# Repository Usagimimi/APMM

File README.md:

# APMM
Mother board for Arduino Pro Mini to work with Mysensors.org

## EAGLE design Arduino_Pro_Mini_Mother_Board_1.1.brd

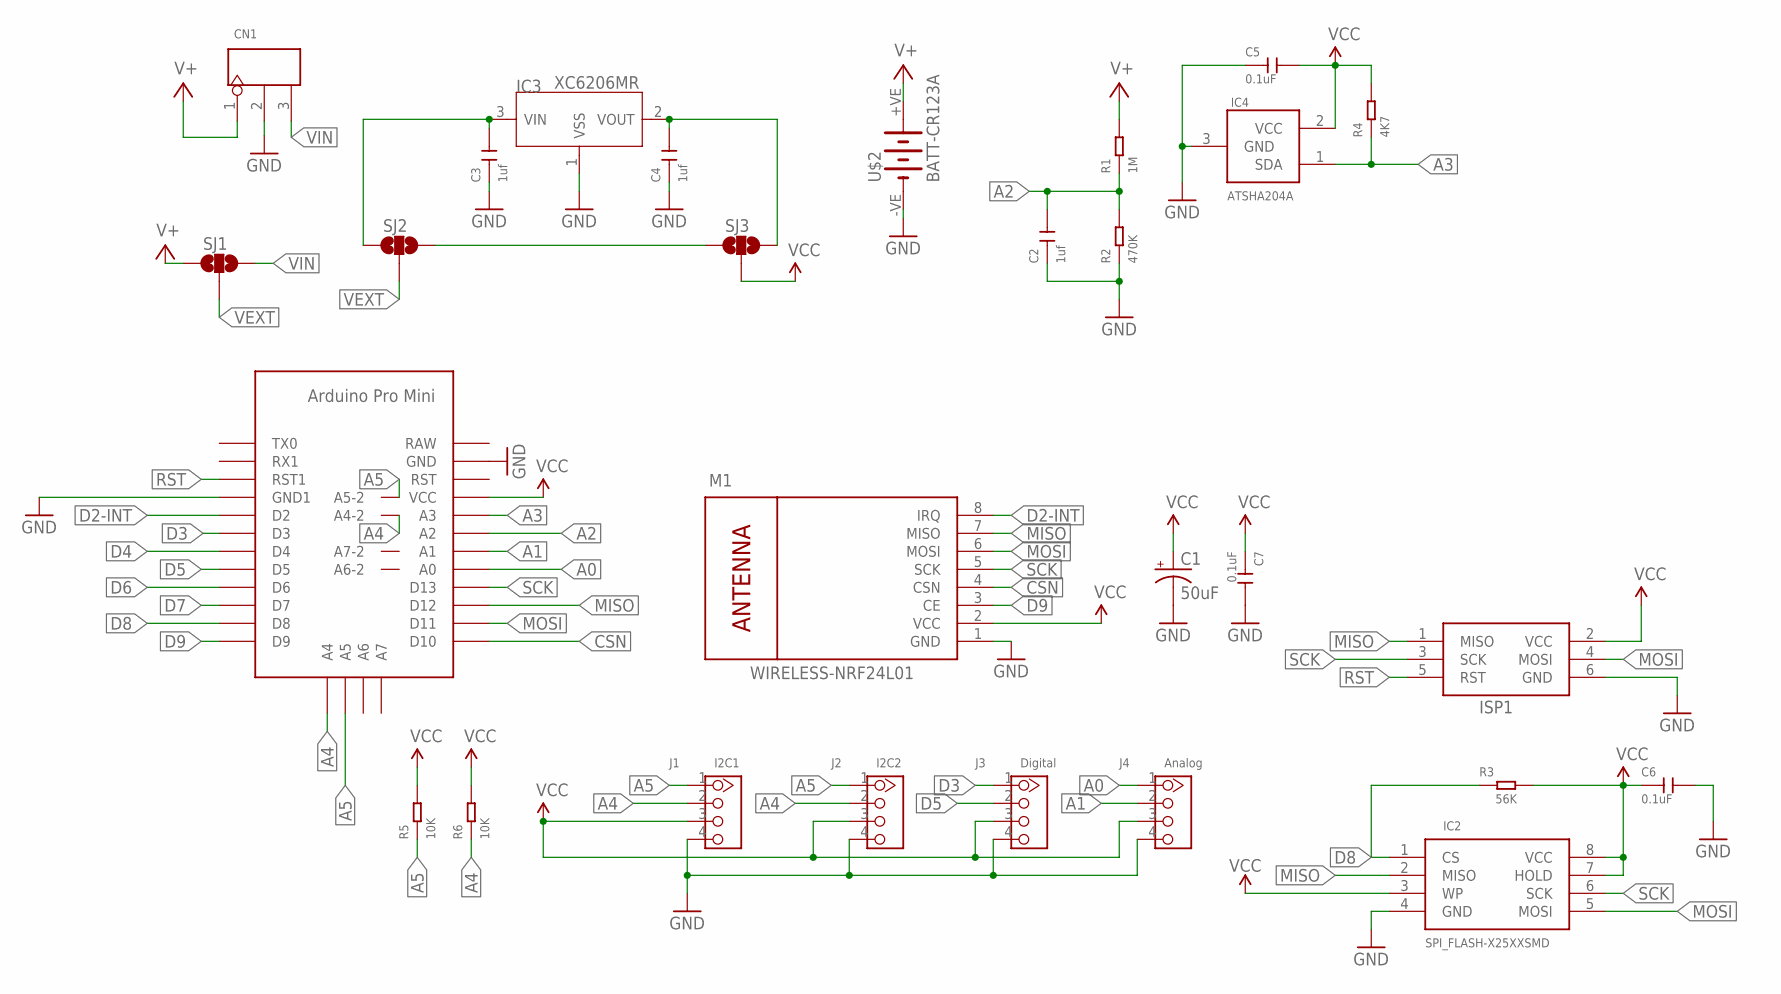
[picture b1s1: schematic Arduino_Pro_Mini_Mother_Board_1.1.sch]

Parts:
ARDUINOPROMINI: PRO-MINI-UNIVERSAL; PRO-MINI-UINIVERSAL
C1: 50uF; EIA6032
C2, C3, C4: 1uf; C0603
C5, C6, C7: 0.1uF; C0603
CN1: DIP-BLACK-MALE-HEADER-VERT(3P-2.54); H3-2.54
IC2: SPI_FLASH-X25XXSMD; SO08
IC3: XC6206MR; SOT23
IC4: ATSHA204A; SOT23
ISP1: AVRISP-6; AVRISP
J1: I2C1; HW4-2.0
J2: I2C2; HW4-2.0
J3: Digital; HW4-2.0
J4: Analog; HW4-2.0
M1: WIRELESS-NRF24L01
R1: 1M; R0603
R2: 470K; R0603
R3: 56K; R0603
R4: 4K7; R0603
R5, R6: 10K; R0603
SJ1, SJ2, SJ3: SOLDERJUMPER_2WAYS; SJ_3
U$2: BATT-CR123A; KEYSTONE-2/3A

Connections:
A0: ARDUINOPROMINI.A0, J4.1
A1: ARDUINOPROMINI.A1, J4.2
A2: ARDUINOPROMINI.A2, C2.2, R1.1, R2.2
A3: ARDUINOPROMINI.A3, IC4.1 (SDA), R4.1
A4: ARDUINOPROMINI.A4, ARDUINOPROMINI.A4-2, J1.2, J2.2, R6.1
A5: ARDUINOPROMINI.A5, ARDUINOPROMINI.A5-2, J1.1, J2.1, R5.1
CSN: ARDUINOPROMINI.D10, M1.4 (CSN)
D2-INT: ARDUINOPROMINI.D2, M1.8 (IRQ)
D3: ARDUINOPROMINI.D3, J3.1
D4: ARDUINOPROMINI.D4
D5: ARDUINOPROMINI.D5, J3.2
D6: ARDUINOPROMINI.D6
D7: ARDUINOPROMINI.D7
D8: ARDUINOPROMINI.D8, IC2.1 (CS), R3.1
D9: ARDUINOPROMINI.D9, M1.3 (CE)
GND: ARDUINOPROMINI.GND0 (GND), ARDUINOPROMINI.GND1, C1.P$2 (-), C2.1, C3.1, C4.1, C5.1, C6.2, C7.2, CN1.2, IC2.4 (GND), IC3.1 (VSS), IC4.3 (GND), ISP1.6 (GND), J1.4, J2.4, J3.4, J4.4, M1.1 (GND), R2.1, U$2.-VE (-)
MISO: ARDUINOPROMINI.D12, IC2.2 (MISO), ISP1.1 (MISO), M1.7 (MISO)
MOSI: ARDUINOPROMINI.D11, IC2.5 (MOSI), ISP1.4 (MOSI), M1.6 (MOSI)
RST: ARDUINOPROMINI.RST1, ISP1.5 (RST)
SCK: ARDUINOPROMINI.D13, IC2.6 (SCK), ISP1.3 (SCK), M1.5 (SCK)
V2: SJ2.3, SJ3.1
V4: C4.2, IC3.2 (VOUT), SJ3.3
V+: CN1.1, R1.2, SJ1.1, U$2.+VE (+)
VCC: ARDUINOPROMINI.VCC, C1.P$1 (+), C5.2, C6.1, C7.1, IC2.3 (WP), IC2.7 (HOLD), IC2.8 (VCC), IC4.2 (VCC), ISP1.2 (VCC), J1.3, J2.3, J3.3, J4.3, M1.2 (VCC), R3.2, R4.2, R5.2, R6.2, SJ3.2
VEXT: SJ1.2, SJ2.2
VIN: C3.2, CN1.3, IC3.3 (VIN), SJ1.3, SJ2.1

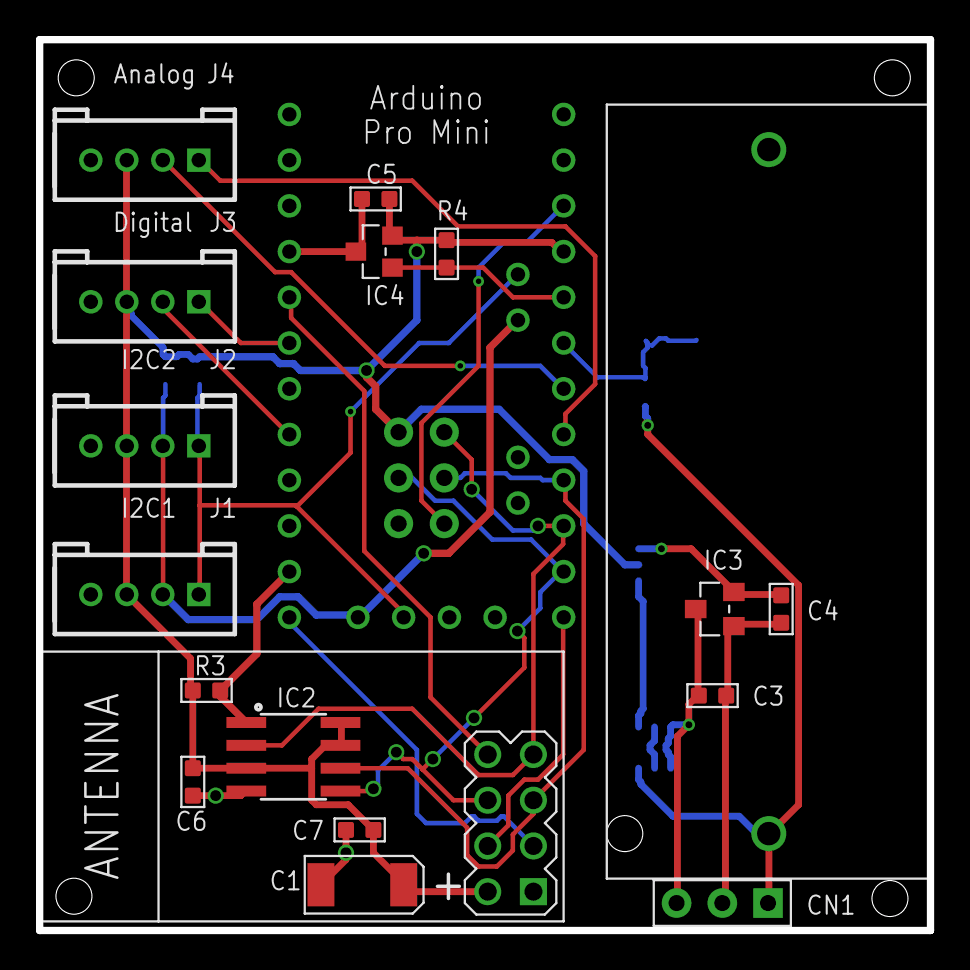
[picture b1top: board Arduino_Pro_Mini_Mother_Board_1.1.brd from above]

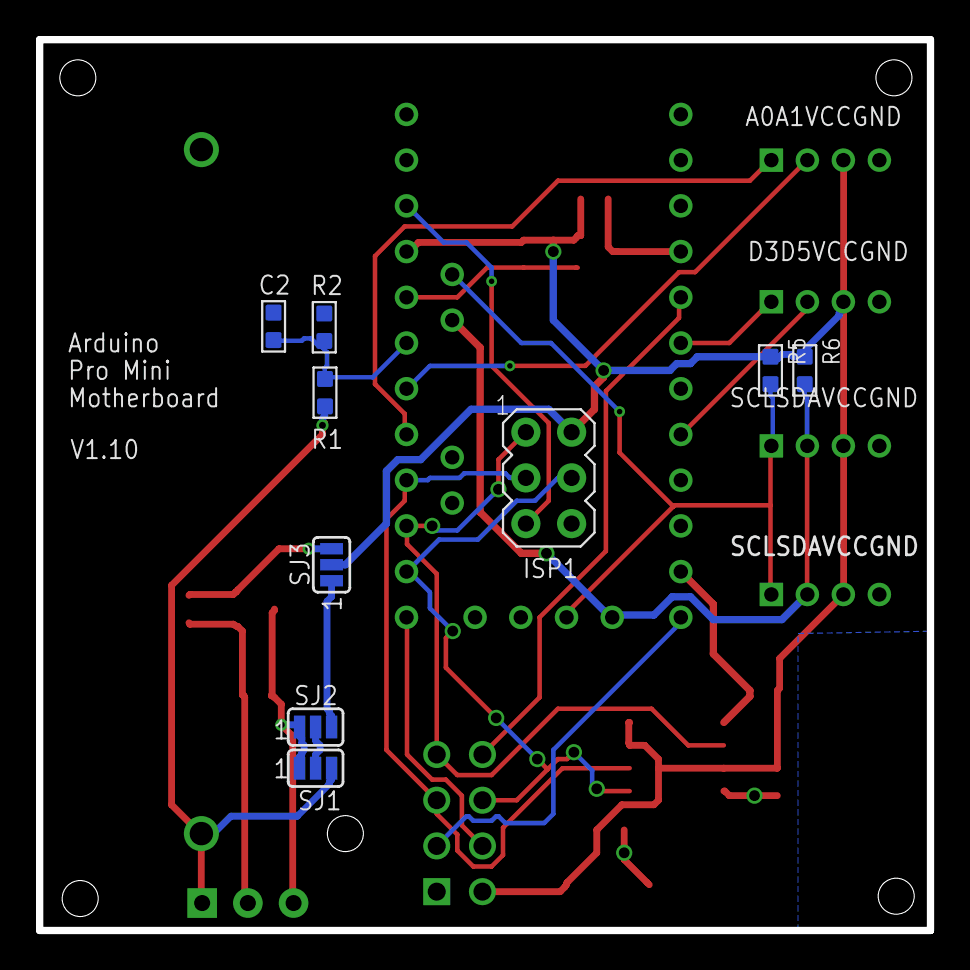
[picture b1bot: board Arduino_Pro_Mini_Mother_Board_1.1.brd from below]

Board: 2 copper layers, 49.5 x 49.5 mm, 28 parts (9 on the bottom side), 23 nets.

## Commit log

2017-02-10 Add files via upload
    Initial commit

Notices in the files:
parts and their libraries:
SparkFun-Capacitors: Licensing: Creative Commons ShareAlike 4.0 International - https://creativecommons.org/licenses/by-sa/4.0
eagle-library-edeca.net-v5: This is v1 and is licensed under the Creative Commons (Attribution-Non-Commercial-Share Alike 2.0 UK)
